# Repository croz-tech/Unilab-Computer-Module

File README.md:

# Unilab Computer Module
This is a clone of the UNILAB BBC Micro computer interface. 

Compatible with all UNILAB modules this allows control from a BBC Micro rateher than the usual 3-Chip-Plus.  This device connects to both PA and PB of the 6522 interface adapter (BBC User Port for input and BBC Printer Port for output).  Credit goes to Louis Higgins who shared detailed photographs of both sides from an original board, enabling this clone to be created.  You'll note that this board is smaller than the original.  While my 3-Chip-Plus clone kept the original board dimensions, this recieved mixed feelings.  In this case I've compressed the board to just 100x100mm to keep it to the $5 level for most board manufacturers. 
 
Example code to read/write these ports from BASIC is included on the schematic.  
## Compatibility:
This board should work fine with the BBC Micro (model B), the B+ range and the Master range, although I think the Master Compact lacks the user port so this is probably incompatible with that machine.

## Notes and Errors:
Note that is the first issue of this schematic/board there are a couple of errors (both to be corrected on a future revision):
1) U3 should be the TTL IC 7416, not 74LS06 as shown on the schematic and PCB skilscreen. 
2) The 3x notches for each of the female connectors (U1 and U4) are on the wrong layer of the PCB design so will be missing on manfuacture.  Use a small round file on the boards to add these notches (shown on the silkscreen) before assembly.

Note also that I have decided to not fit the diodes D2 and D3 from the CB1/CB2 ports to VREF on my first build.  While this might make sense to clamp the H1/H2 inputs (converting to TTL levels safe for the Beeb) I'm concerned that CB1/CB2 can be driven as outputs which might stress the 6522.  Will check on the 6522 datasheet and address this later.

## Connection:
The module connects to the Beeb's User and Printer ports using a 20-way and 26-way IDC ribbon cables respectively.  Unlike the original I've gone with IDC headers rather than IDC solder terminators on the PCB since these are becoming more difficult to get hold of and it means the cables can be entirely removed from the board for easier storage.    I've made the cable around 0.5m length and these are 1:1 cables (pin numbering identical at either end).  The unit takes its power from the Beeb's User Port and can also power UNILAB peripheral boards.  The board is fitted with a 500mA polyfuse to protect the Beeb from any short circuits (the original boards used a 1/4 inch glass fuse).

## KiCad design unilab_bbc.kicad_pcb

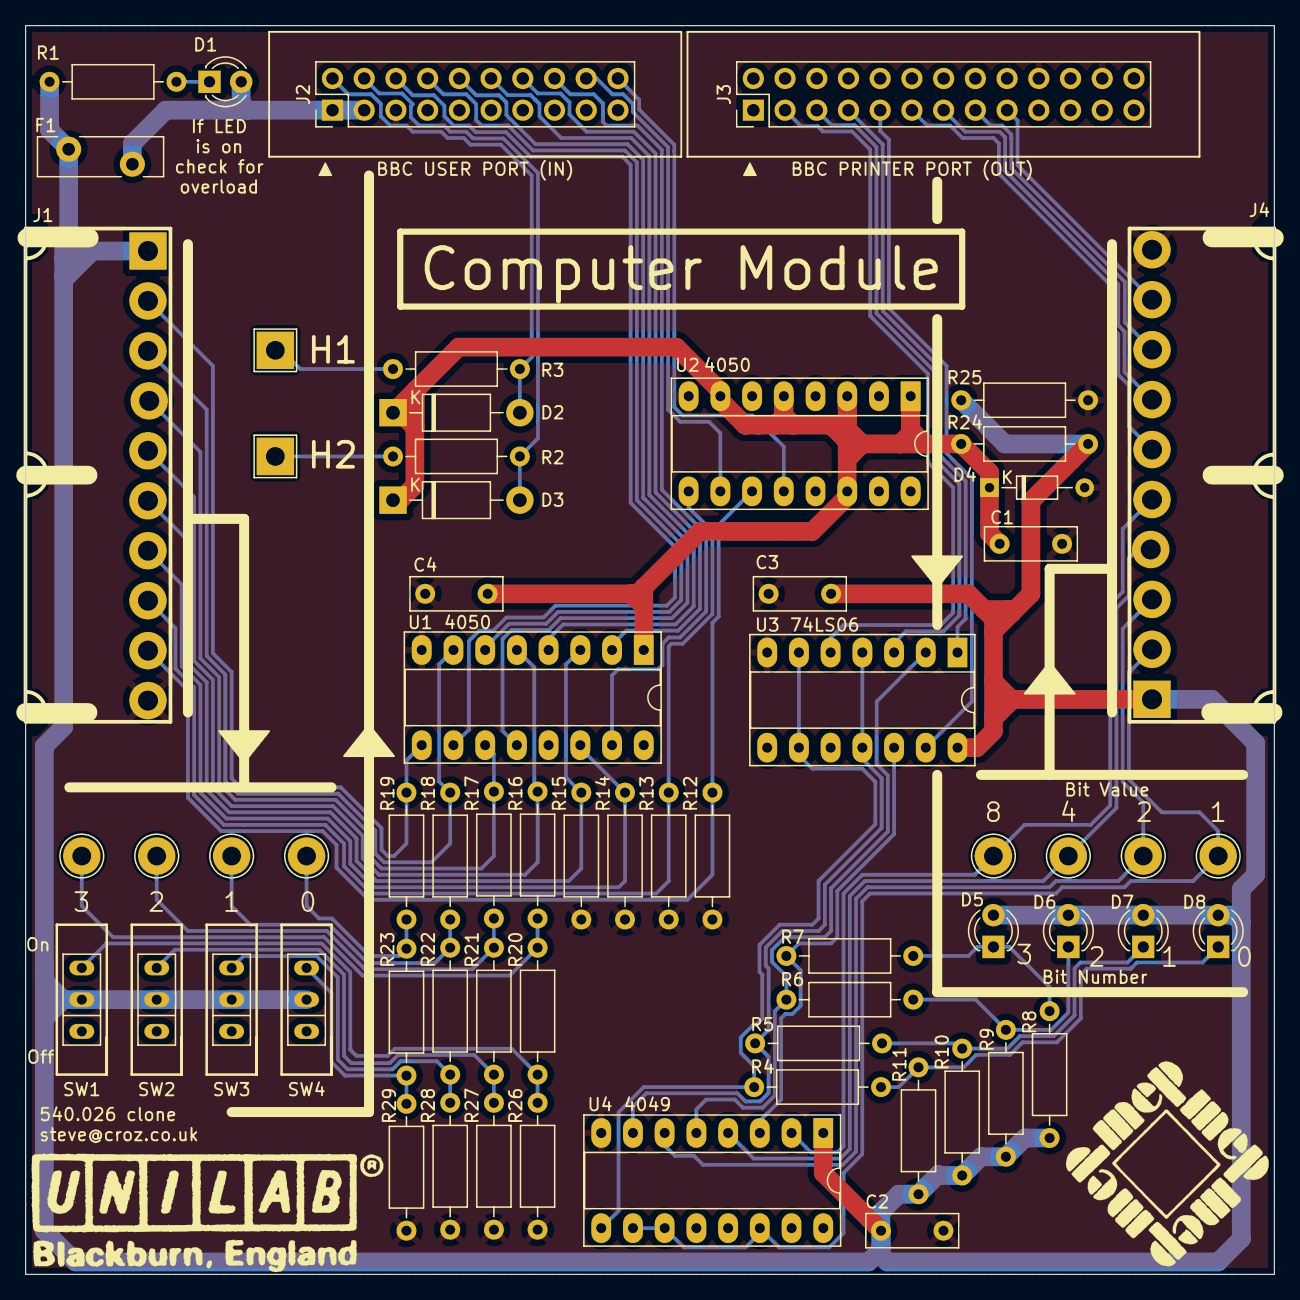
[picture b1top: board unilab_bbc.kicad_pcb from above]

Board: 2 copper layers, 100.0 x 100.0 mm, 64 parts (0 on the bottom side), 53 nets.

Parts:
C1, C2, C3, C4: 100n; C_Rect_L7.2mm_W2.5mm_P5.00mm_FKS2_FKP2_MKS2_MKP2
D1: 'FUSE' RED; LED_D3.0mm
D2, D3: 1N4001; D_DO-41_SOD81_P10.16mm_Horizontal
D4: 3V0; D_DO-34_SOD68_P7.62mm_Horizontal
D5: '8' RED; LED_D3.0mm
D6: '4' RED; LED_D3.0mm
D7: '2' YEL; LED_D3.0mm
D8: '1' GRN; LED_D3.0mm
F1: 500mA; Fuse_Bourns_MF-RG400
J1: PORT A; 10W_RA_Female
J2: BBC USER PORT (IN); PinHeader_2x10_P2.54mm_Vertical
J3: BBC PRINTER PORT (OUT); PinHeader_2x13_P2.54mm_Vertical
J4: PORT B; 10W_RA_Female
R1: 100R; R_Axial_DIN0207_L6.3mm_D2.5mm_P10.16mm_Horizontal
R2, R3, R25: 220R; R_Axial_DIN0207_L6.3mm_D2.5mm_P10.16mm_Horizontal
R4, R5, R6, R7: 110R; R_Axial_DIN0207_L6.3mm_D2.5mm_P10.16mm_Horizontal
R8, R9, R10, R11: 680R; R_Axial_DIN0207_L6.3mm_D2.5mm_P10.16mm_Horizontal
R12, R13, R14, R15, R16, R17, R18, R19, R20, R21, R22, R23: 220K; R_Axial_DIN0207_L6.3mm_D2.5mm_P10.16mm_Horizontal
R24: 390R; R_Axial_DIN0207_L6.3mm_D2.5mm_P10.16mm_Horizontal
R26, R27, R28, R29: 10K; R_Axial_DIN0207_L6.3mm_D2.5mm_P10.16mm_Horizontal
SW1: 3; SPDT SIP SLIDE
SW2: 2; SPDT SIP SLIDE
SW3: 1; SPDT SIP SLIDE
SW4: 0; SPDT SIP SLIDE
TP1: H1; TestPoint_THTPad_3.0x3.0mm_Drill1.5mm
TP2: H2; TestPoint_THTPad_3.0x3.0mm_Drill1.5mm
TP3: 8; TestPoint_THTPad_D3.0mm_Drill1.5mm
TP4: 4; TestPoint_THTPad_D3.0mm_Drill1.5mm
TP5, TP8: 2; TestPoint_THTPad_D3.0mm_Drill1.5mm
TP6, TP9: 1; TestPoint_THTPad_D3.0mm_Drill1.5mm
TP7: 3; TestPoint_THTPad_D3.0mm_Drill1.5mm
TP10: 0; TestPoint_THTPad_D3.0mm_Drill1.5mm
U1, U2: 4050; DIP-16_W7.62mm_Socket_LongPads
U3: 74LS06; DIP-14_W7.62mm_Socket_LongPads
U4: 4049; DIP-16_W7.62mm_Socket_LongPads

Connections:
+5V: C2.1, C3.1, D5.2 (A), D6.2 (A), D7.2 (A), D8.2 (A), F1.2, J1.1, J4.1, R1.2, R8.1, R9.1, R10.1, R11.1, R24.1, R25.1, SW1.2 (B), SW2.2 (B), SW3.2 (B), SW4.2 (B), U3.14 (VCC), U4.1 (VCC)
/CB1: D2.2 (A), J2.2, R3.2
/CB2: D3.2 (A), J2.4, R2.2
/D0: J3.3, U3.5
/D1: J3.5, U3.3
/D2: J3.7, U3.1
/D3: J3.9, U3.13
/D4: J3.11, J4.6
/D5: J3.13, J4.7
/D6: J3.15, J4.8
/D7: J3.17, J4.9
/PB0: J2.6, U1.10
/PB1: J2.8, U1.6
/PB2: J2.10, U1.12
/PB3: J2.12, U1.4
/PB4: J2.14, U1.2
/PB5: J2.16, U1.15
/PB6: J2.18, U2.10
/PB7: J2.20, U2.12
/VREF: C1.1, C4.1, D2.1 (K), D3.1 (K), D4.1 (K), R24.2, U1.1 (VCC), U2.1 (VCC), U2.3, U2.5, U2.7, U2.14
GND: C1.2, C2.2, C3.2, C4.2, D4.2 (A), J1.10, J2.5, J3.20, J3.24, J4.10, R12.1, R13.1, R14.1, R15.1, R25.2, R26.1, R27.1, R28.1, R29.1, U1.8 (VSS), U2.8 (VSS), U3.7 (GND), U4.8 (VSS)
unnamed: D1.1 (K), R1.1
unnamed: D1.2 (A), F1.1, J2.1, J2.3
unnamed: D5.1 (K), R7.1, R8.2
unnamed: D6.1 (K), R6.1, R9.2
unnamed: D7.1 (K), R5.1, R10.2
unnamed: D8.1 (K), R4.1, R11.2
unnamed: J1.2, R19.2, U1.9
unnamed: J1.3, R18.2, U1.7
unnamed: J1.4, R17.2, U1.11
unnamed: J1.5, R16.2, U1.5
unnamed: J1.6, R15.2, U1.3
unnamed: J1.7, R14.2, U1.14
unnamed: J1.8, R13.2, U2.9
unnamed: J1.9, R12.2, U2.11
unnamed: J4.2, TP6.1, U4.10, U4.11, U4.14
unnamed: J4.3, TP5.1, U4.6
unnamed: J4.4, TP4.1, U4.4
unnamed: J4.5, TP3.1, U4.2
unnamed: R2.1, TP2.1
unnamed: R3.1, TP1.1
unnamed: R4.2, U3.6, U3.9, U4.9
unnamed: R5.2, U3.4, U3.11, U4.7
unnamed: R6.2, U3.2, U4.5
unnamed: R7.2, U3.12, U4.3
unnamed: R16.1, R20.2, TP7.1
unnamed: R17.1, R21.2, TP8.1
unnamed: R18.1, R22.2, TP9.1
unnamed: R19.1, R23.2, TP10.1
unnamed: R20.1, R26.2, SW1.3 (C)
unnamed: R21.1, R27.2, SW2.3 (C)
unnamed: R22.1, R28.2, SW3.3 (C)
unnamed: R23.1, R29.2, SW4.3 (C)

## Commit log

2023-07-02 Initial version (MK II a)
2023-07-02 Added pics
2023-07-02 Updated README.md
    Added more description and a picture
